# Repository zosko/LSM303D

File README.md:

# LSM303D
LSM303D module

The LSM303D module is a small electronic sensor used to measure motion and magnetic fields. It combines two important sensors in one device: a three-axis accelerometer and a three-axis magnetometer. The accelerometer measures movement, tilt, and vibration along the X, Y, and Z axes. At the same time, the magnetometer measures the strength and direction of the Earth’s magnetic field. Because of this combination, the module can be used as a digital compass to determine orientation and direction.

The LSM303D module is often used in robotics, drones, navigation systems, and mobile devices. It communicates with microcontrollers through I2C or SPI communication protocols, which makes it easy to connect to platforms such as Arduino or Raspberry Pi. The module also has low power consumption, which makes it suitable for battery-powered projects and portable electronics.

Developers use the sensor data from the module to calculate heading, orientation, and motion. However, calibration is usually necessary to improve the accuracy of the magnetometer readings. With proper calibration and programming, the LSM303D can provide reliable and precise measurements. Because of its versatility and compact design, the LSM303D module is widely used in educational projects, embedded systems, and advanced motion-tracking applications.

## Scheme

## Board

## Sponsorship

This project is kindly sponsored by [PCBWay](https://pcbway.com).
PCBWay specializes in manufacturing high-quality PCBs and makes them affordable to hobbyist and professionals alike.

The range of services they offer include PCB prototyping, assembly, instant quotes for your order, a verification process by a team
of experts and an easy to use, hassle-free order process.

I'm grateful to PCBWay for the support in creating this project.

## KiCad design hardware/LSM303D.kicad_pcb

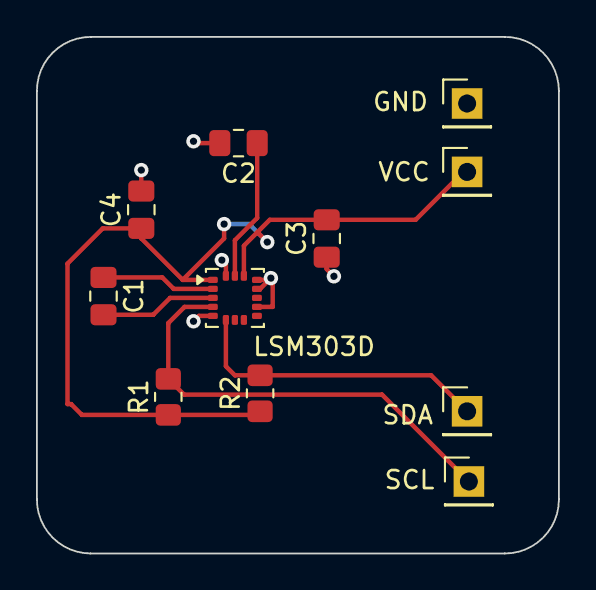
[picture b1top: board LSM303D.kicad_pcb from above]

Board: 2 copper layers, 29.0 x 28.7 mm, 11 parts (0 on the bottom side), 7 nets.

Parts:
C1: 220nF; C_0805_2012Metric_Pad1.18x1.45mm_HandSolder
C2: 4.7uF; C_0805_2012Metric_Pad1.18x1.45mm_HandSolder
C3: 100nF; C_0805_2012Metric_Pad1.18x1.45mm_HandSolder
C4: 10nF; C_0805_2012Metric_Pad1.18x1.45mm_HandSolder
GND: GND; PinHeader_1x01_P2.54mm_Vertical
LSM303D: LSM303D; LGA-16_3x3mm_P0.5mm_LayoutBorder3x5y
R1, R2: 4.7K; R_0805_2012Metric_Pad1.20x1.40mm_HandSolder
SCL: SCL; PinHeader_1x01_P2.54mm_Vertical
SDA: SDA; PinHeader_1x01_P2.54mm_Vertical
VCC: 3.3V; PinHeader_1x01_P2.54mm_Vertical

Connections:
3.3V: C3.2, C4.1, LSM303D.1 (VDDIO), LSM303D.14 (VDD), R1.1, R2.1, VCC.1
GND: C2.2, C3.1, C4.2, GND.1, LSM303D.5 (GND), LSM303D.10 (GND), LSM303D.12 (GND), LSM303D.13 (GND), LSM303D.16 (GND)
unnamed: C2.1, LSM303D.15 (C1)
unnamed: C1.1, LSM303D.2 (SETC)
unnamed: C1.2, LSM303D.3 (SETP)
SCL: LSM303D.4 (SCL/SPC), R1.2, SCL.1
SDA: LSM303D.6 (SDA/SDI/SDO), R2.2, SDA.1

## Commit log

2025-12-27 fix footprint
